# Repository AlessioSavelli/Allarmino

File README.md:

# Welcome to Allarmino  

Benvenuti nel progetto **Allarmino**! Qui troverai tutti i sorgenti **Hardware**, **Software** e **Firmware** necessari per creare e utilizzare il tuo Allarmino.

---

## 📚 **Riferimenti nelle riviste ElettronicaIN**

- 📖 **[Rivista Nr264](https://futuranet.it/prodotto/n-264-maggio-2022/)**: Introduzione alla **main board Allarmino**, basata su ESP32.
- 📖 **[Rivista Nr271](https://futuranet.it/prodotto/n-271-febbraio-2023-marzo-2023)**: Dettagli sulla **scheda di espansione 01** e il primo approccio al software **AllarminoIDE**.

---

## 💾 **Firmware disponibili per ESP32**

| Versione      | Stato            |
|---------------|------------------|
| V1.0          | Disponibile      |
| V1.1.2        | Disponibile      |
| V1.1.3        | Disponibile      |
### ❌ Firmware non più disponibili:

| Versione      | Stato            |
|---------------|------------------|
| V1.1          | Deprecato        |
| V1.1.1        | Deprecato        |

---

## 🖥️ **Software disponibili**

| Versione      | Testato su                   |
|---------------|------------------------------|
| V1.0.0.2      | Win10 64-bit, Win11 64-bit   |

### ❌ Software non più disponibili:

| Versione      | Testato su                   |
|---------------|------------------------------|
| V1.0          | Win11 64-bit                 |
| V1.0.0.1      | Win10 64-bit, Win11 64-bit   |

---

## 🔧 **Hardware disponibili**

| Componente            | Dettagli                                   |
|-----------------------|-------------------------------------------|
| Allarmino Main Board  | Basata su ESP32                           |
| Espansione 01         | CAN BUS 2.0B + Ethernet (W5500, ENC28J60) |

📄 **[Datasheet disponibile (CLICCA QUI)](https://github.com/AlessioSavelli/Allarmino/tree/main/Datasheet/Allarmino/)**

---

## 📝 **Licenza**

### MIT License - Software
Copyright (c) 2022 Alessio Savelli FuturaGroup

Con la presente si concede, a chiunque ottenga una copia di questo software e dei file di documentazione associati (il "Software"), l'autorizzazione a usare gratuitamente il Software senza alcuna limitazione, compresi i diritti di usare, copiare, modificare, unire, pubblicare, distribuire, cedere in sottolicenza e/o vendere copie del Software, nonché di permettere ai soggetti cui il Software è fornito di fare altrettanto, alle seguenti condizioni:

L'avviso di copyright indicato sopra e questo avviso di autorizzazione devono essere inclusi in ogni copia o parte sostanziale del Software.

IL SOFTWARE VIENE FORNITO "COSÌ COM'È", SENZA GARANZIE DI ALCUN TIPO, ESPLICITE O IMPLICITE.

### MIT License - Hardware
Copyright (c) 2022 Alessio Savelli FuturaGroup

Con la presente si concede, a chiunque ottenga una copia di questo hardware e dei file di documentazione associati (l'"Hardware"), l'autorizzazione a usare gratuitamente l'Hardware senza alcuna limitazione, compresi i diritti di usare, copiare, modificare, unire, pubblicare, distribuire, cedere in sottolicenza e/o vendere copie dell'Hardware, nonché di permettere ai soggetti cui l'Hardware è fornito di fare altrettanto, alle seguenti condizioni:

L'avviso di copyright indicato sopra e questo avviso di autorizzazione devono essere inclusi in ogni copia o parte sostanziale dell'Hardware.

L'HARDWARE VIENE FORNITO "COSÌ COM'È", SENZA GARANZIE DI ALCUN TIPO, ESPLICITE O IMPLICITE.

---

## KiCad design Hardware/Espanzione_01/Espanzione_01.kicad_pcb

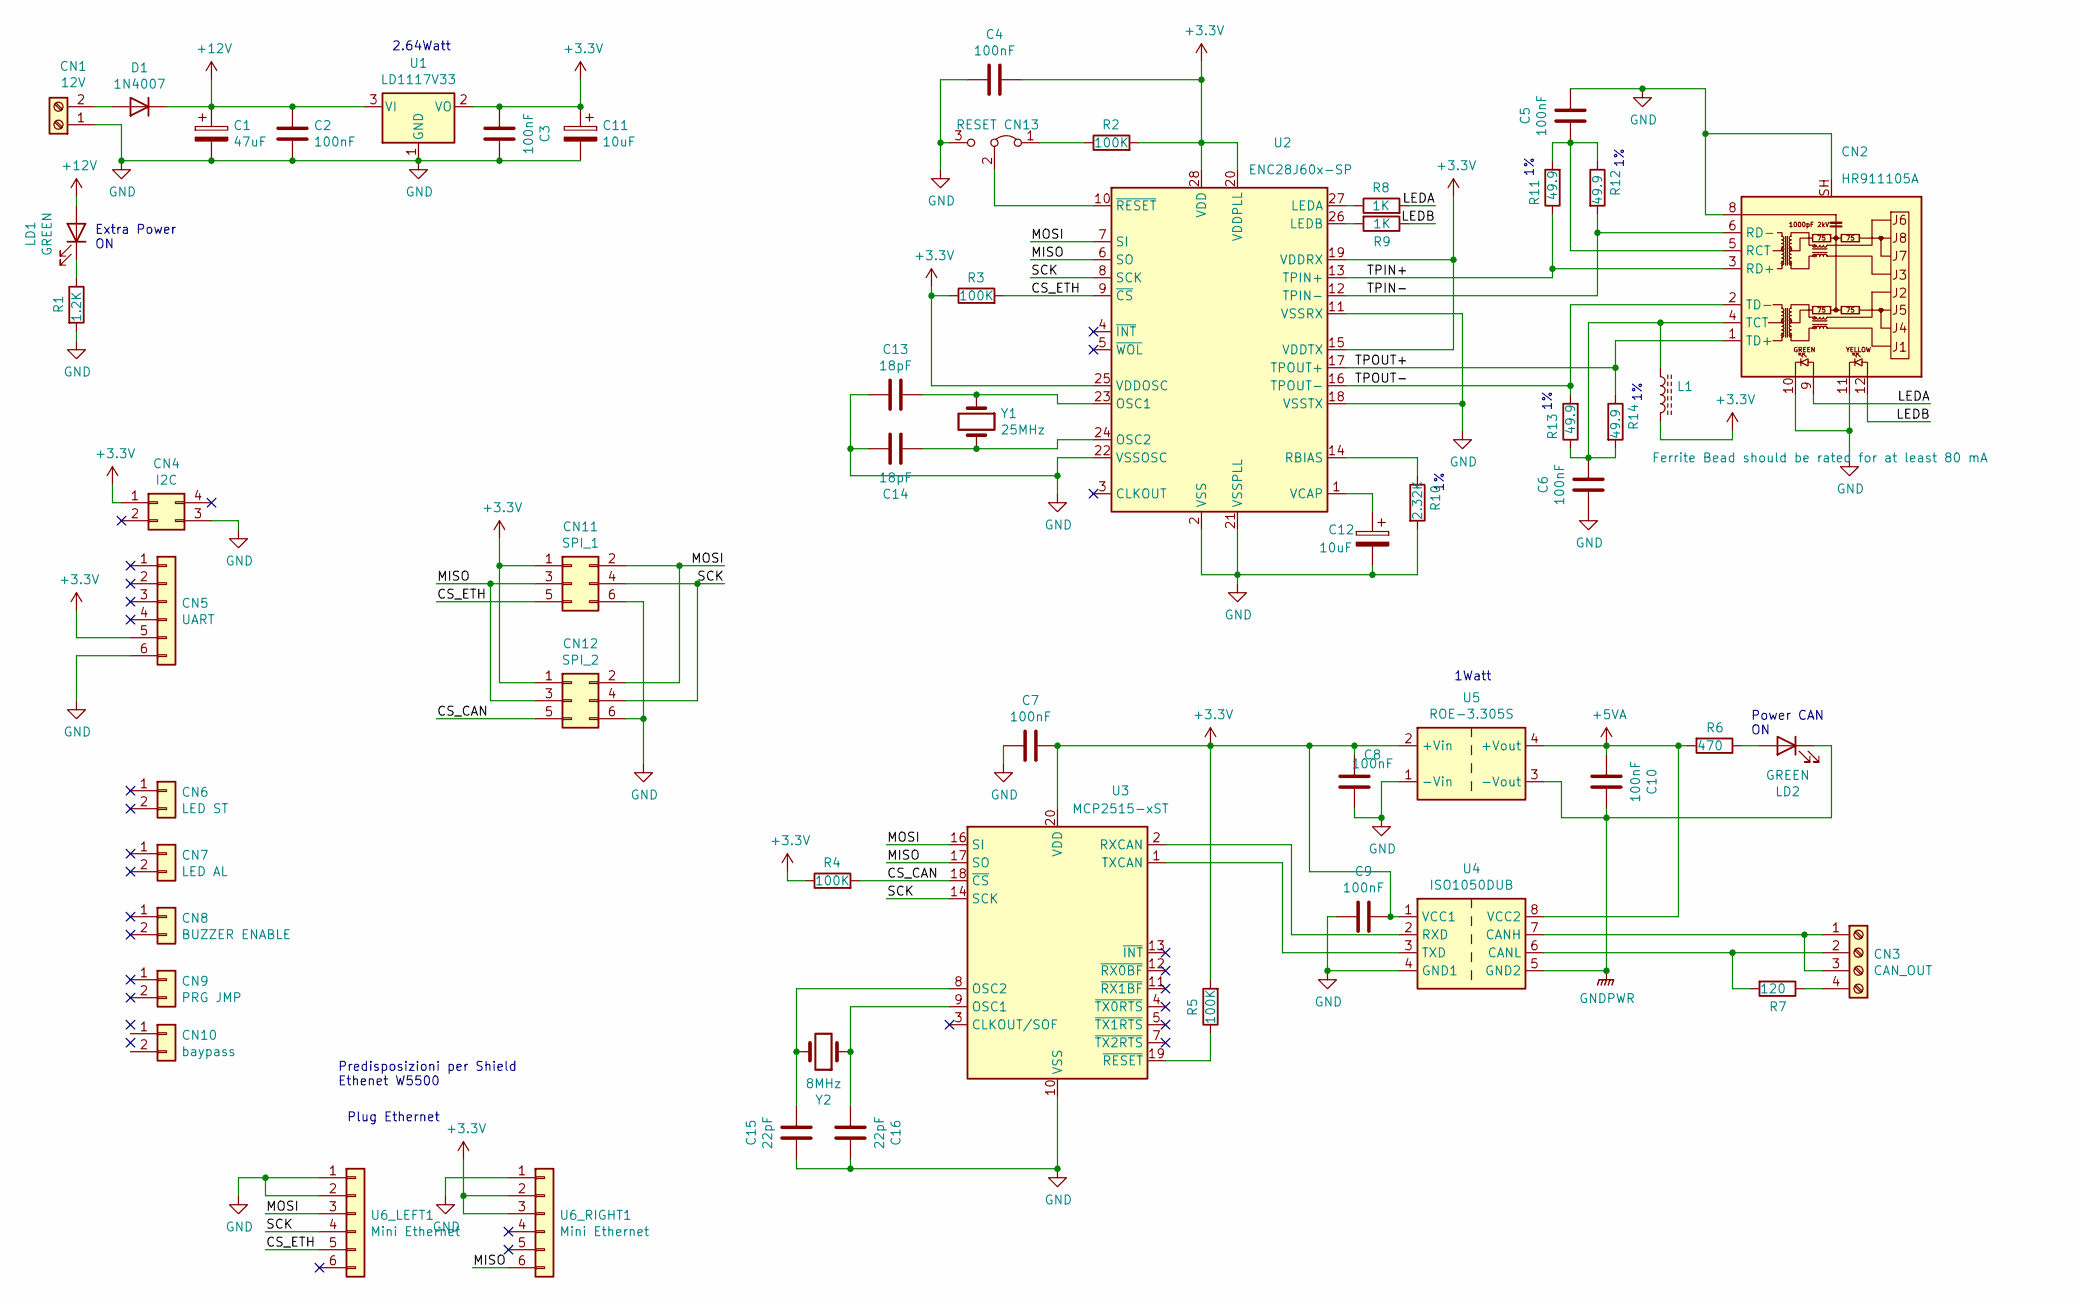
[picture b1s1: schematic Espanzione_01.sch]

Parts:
C1: 47uF; CP_Radial_D8.0mm_P3.50mm
C2, C3, C4, C5, C6, C7, C8, C9, C10: 100nF; C_Disc_D4.7mm_W2.5mm_P5.00mm
C11, C12: 10uF; CP_Radial_D5.0mm_P2.50mm
C13, C14: 18pF; C_Disc_D4.7mm_W2.5mm_P5.00mm
C15, C16: 22pF; C_Disc_D4.7mm_W2.5mm_P5.00mm
CN1: 12V; TerminalBlock_bornier-2_P5.08mm
CN2: HR911105A; RJ45_Wuerth_7499010121A_Horizontal
CN3: CAN_OUT; TerminalBlock_bornier-4_P5.08mm
CN4: I2C; PinHeader_2x02_P2.54mm_Vertical
CN5: UART; PinHeader_1x06_P2.54mm_Vertical
CN6: LED ST; PinHeader_1x02_P2.54mm_Vertical
CN7: LED AL; PinHeader_1x02_P2.54mm_Vertical
CN8: BUZZER ENABLE; PinHeader_1x02_P2.54mm_Vertical
CN9: PRG JMP; PinHeader_1x02_P2.54mm_Vertical
CN10: baypass; PinHeader_1x02_P2.54mm_Vertical
CN11: SPI_1; PinHeader_2x03_P2.54mm_Vertical
CN12: SPI_2; PinHeader_2x03_P2.54mm_Vertical
CN13: RESET; SolderJumper-3_P1.3mm_Bridged12_Pad1.0x1.5mm_NumberLabels
D1: 1N4007; D_DO-41_SOD81_P5.08mm_Vertical_KathodeUp
L1: Ferrite Bead should be rated for at least 80 mA; L_Axial_L7.0mm_D3.3mm_P2.54mm_Vertical_Fastron_MICC
LD1, LD2: GREEN; LED_D3.0mm
R1: 1.2K; R_Axial_DIN0207_L6.3mm_D2.5mm_P2.54mm_Vertical
R2, R3, R4, R5: 100K; R_Axial_DIN0207_L6.3mm_D2.5mm_P2.54mm_Vertical
R6: 470; R_Axial_DIN0207_L6.3mm_D2.5mm_P2.54mm_Vertical
R7: 120; R_Axial_DIN0207_L6.3mm_D2.5mm_P2.54mm_Vertical
R8, R9: 1K; R_Axial_DIN0207_L6.3mm_D2.5mm_P2.54mm_Vertical
R10: 2.32K; R_Axial_DIN0207_L6.3mm_D2.5mm_P2.54mm_Vertical
R11, R12, R13, R14: 49.9; R_Axial_DIN0207_L6.3mm_D2.5mm_P2.54mm_Vertical
U1: LD1117V33; TO-220-3_Horizontal_TabDown
U2: ENC28J60x-SP; DIP-28_W7.62mm
U3: MCP2515-xST; TSSOP-20_4.4x6.5mm_P0.65mm
U4: ISO1050DUB; DIP-8_W7.62mm_Socket
U5: ROE-3.305S; Converter_DCDC_Murata_MEE1SxxxxSC_THT
U6_LEFT1, U6_RIGHT1: Mini Ethernet; PinHeader_1x06_P2.54mm_Vertical
Y1: 25MHz; Crystal_HC49-4H_Vertical
Y2: 8MHz; Crystal_HC49-4H_Vertical

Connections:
+3.3VA: C10.2, R6.2, U4.8 (VCC2), U5.4 (+Vout)
+3V3: C3.2, C4.1, C7.2, C8.1, C9.1, C11.1, CN4.1, CN5.5, CN11.1, CN12.1, L1.2, R2.2, R3.1, R4.1, R5.2, U1.2 (VO), U2.15 (VDDTX), U2.19 (VDDRX), U2.20 (VDDPLL), U2.25 (VDDOSC), U2.28 (VDD), U3.20 (VDD), U4.1 (VCC1), U5.2 (+Vin), U6_RIGHT1.2, U6_RIGHT1.3
+12V: C1.1, C2.1, D1.1 (K), LD1.2 (A), U1.3 (VI)
/CS_CAN: CN12.5, R4.2, U3.18 (~CS)
/CS_ETH: CN11.5, R3.2, U2.9 (~CS), U6_LEFT1.5
/LEDA: CN2.9, R8.2
/LEDB: CN2.12, R9.1
/MISO: CN11.3, CN12.3, U2.6 (SO), U3.17 (SO), U6_RIGHT1.6
/MOSI: CN11.2, CN12.2, U2.7 (SI), U3.16 (SI), U6_LEFT1.3
/SCK: CN11.4, CN12.4, U2.8 (SCK), U3.14 (SCK), U6_LEFT1.4
/TPIN+: CN2.3 (RD+), R11.1, U2.13 (TPIN+)
/TPIN-: CN2.6 (RD-), R12.2, U2.12 (TPIN-)
/TPOUT+: CN2.1 (TD+), R14.1, U2.17 (TPOUT+)
/TPOUT-: CN2.2 (TD-), R13.2, U2.16 (TPOUT-)
GND: C1.2, C2.2, C3.1, C4.2, C5.1, C6.2, C7.1, C8.2, C9.2, C11.2, C12.2, C13.2, C14.1, C15.2, C16.1, CN1.1, CN2.8, CN2.10, CN2.11, CN2.SH, CN4.3, CN5.6, CN11.6, CN12.6, CN13.3 (B), R1.2, R10.2, U1.1 (GND), U2.2 (VSS), U2.11 (VSSRX), U2.18 (VSSTX), U2.21 (VSSPLL), U2.22 (VSSOSC), U3.10 (VSS), U4.4 (GND1), U5.1 (-Vin), U6_LEFT1.1, U6_LEFT1.2, U6_RIGHT1.1
GNDPWR: C10.1, LD2.1 (K), U4.5 (GND2), U5.3 (-Vout)
unnamed: C5.2, CN2.5 (RCT), R11.2, R12.1
unnamed: C6.1, CN2.4 (TCT), L1.1, R13.1, R14.2
unnamed: C12.1, U2.1 (VCAP)
unnamed: C13.1, U2.23 (OSC1), Y1.1
unnamed: C14.2, U2.24 (OSC2), Y1.2
unnamed: C15.1, U3.8 (OSC2), Y2.2
unnamed: C16.2, U3.9 (OSC1), Y2.1
unnamed: CN1.2, D1.2 (A)
unnamed: CN3.1, CN3.3, U4.7 (CANH)
unnamed: CN3.2, R7.2, U4.6 (CANL)
unnamed: CN3.4, R7.1
unnamed: CN13.1 (A), R2.1
unnamed: CN13.2 (C), U2.10 (~RESET)
unnamed: LD1.1 (K), R1.1
unnamed: LD2.2 (A), R6.1
unnamed: R5.1, U3.19 (~RESET)
unnamed: R8.1, U2.27 (LEDA)
unnamed: R9.2, U2.26 (LEDB)
unnamed: R10.1, U2.14 (RBIAS)
unnamed: U3.1 (TXCAN), U4.3 (TXD)
unnamed: U3.2 (RXCAN), U4.2 (RXD)

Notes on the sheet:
2.64Watt
Extra Power ON
Power CAN ON
1Watt
Predisposizioni per Shield Ethenet W5500
Plug Ethernet

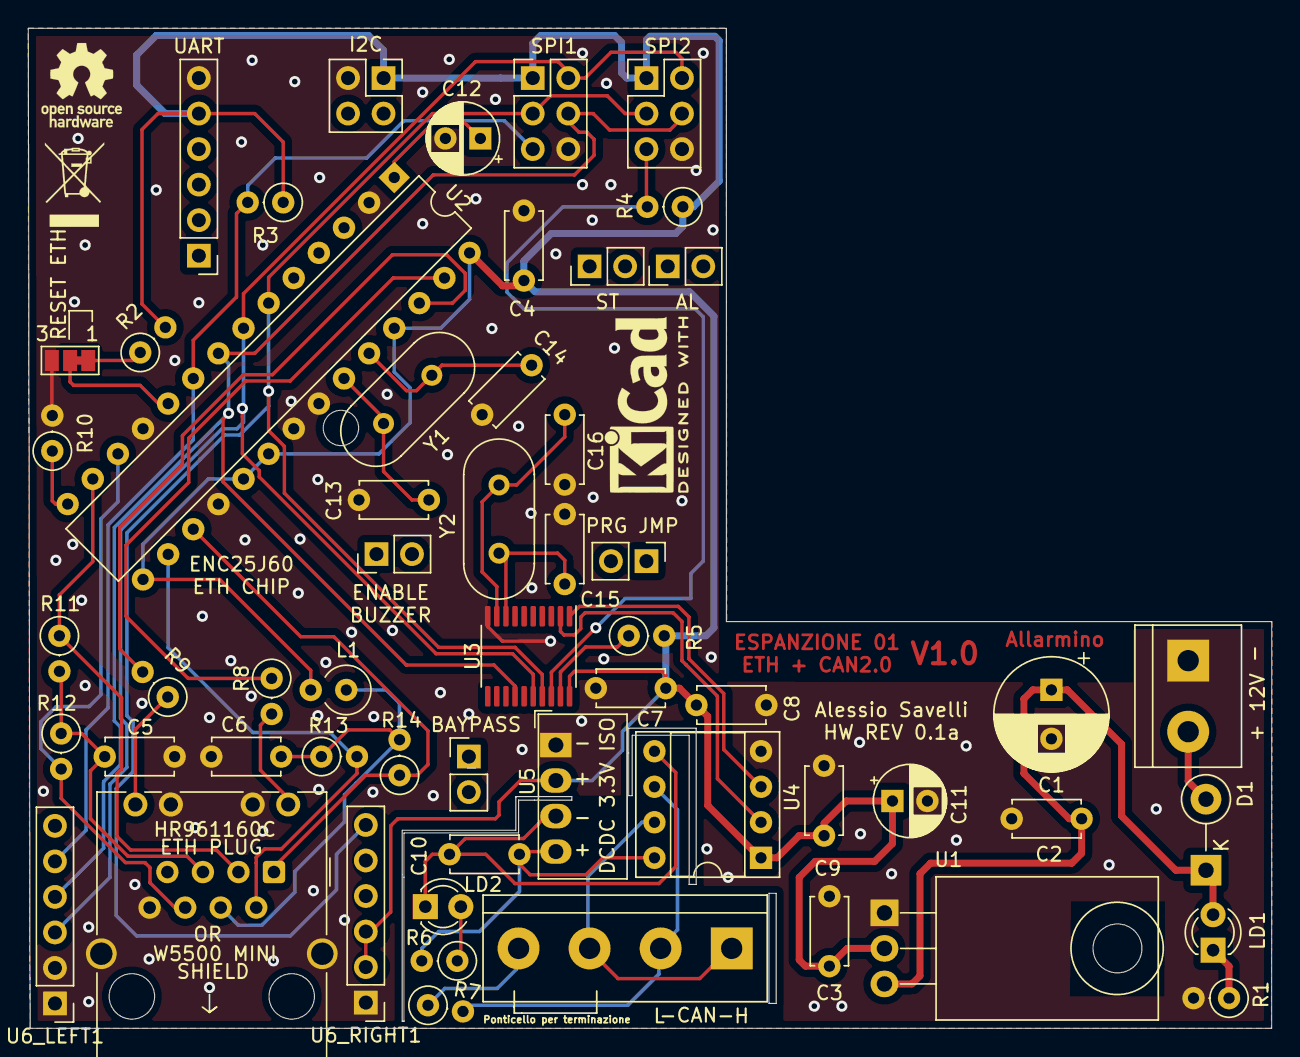
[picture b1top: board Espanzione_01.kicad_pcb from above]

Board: 2 copper layers, 88.9 x 71.5 mm, 56 parts (0 on the bottom side), 37 nets.

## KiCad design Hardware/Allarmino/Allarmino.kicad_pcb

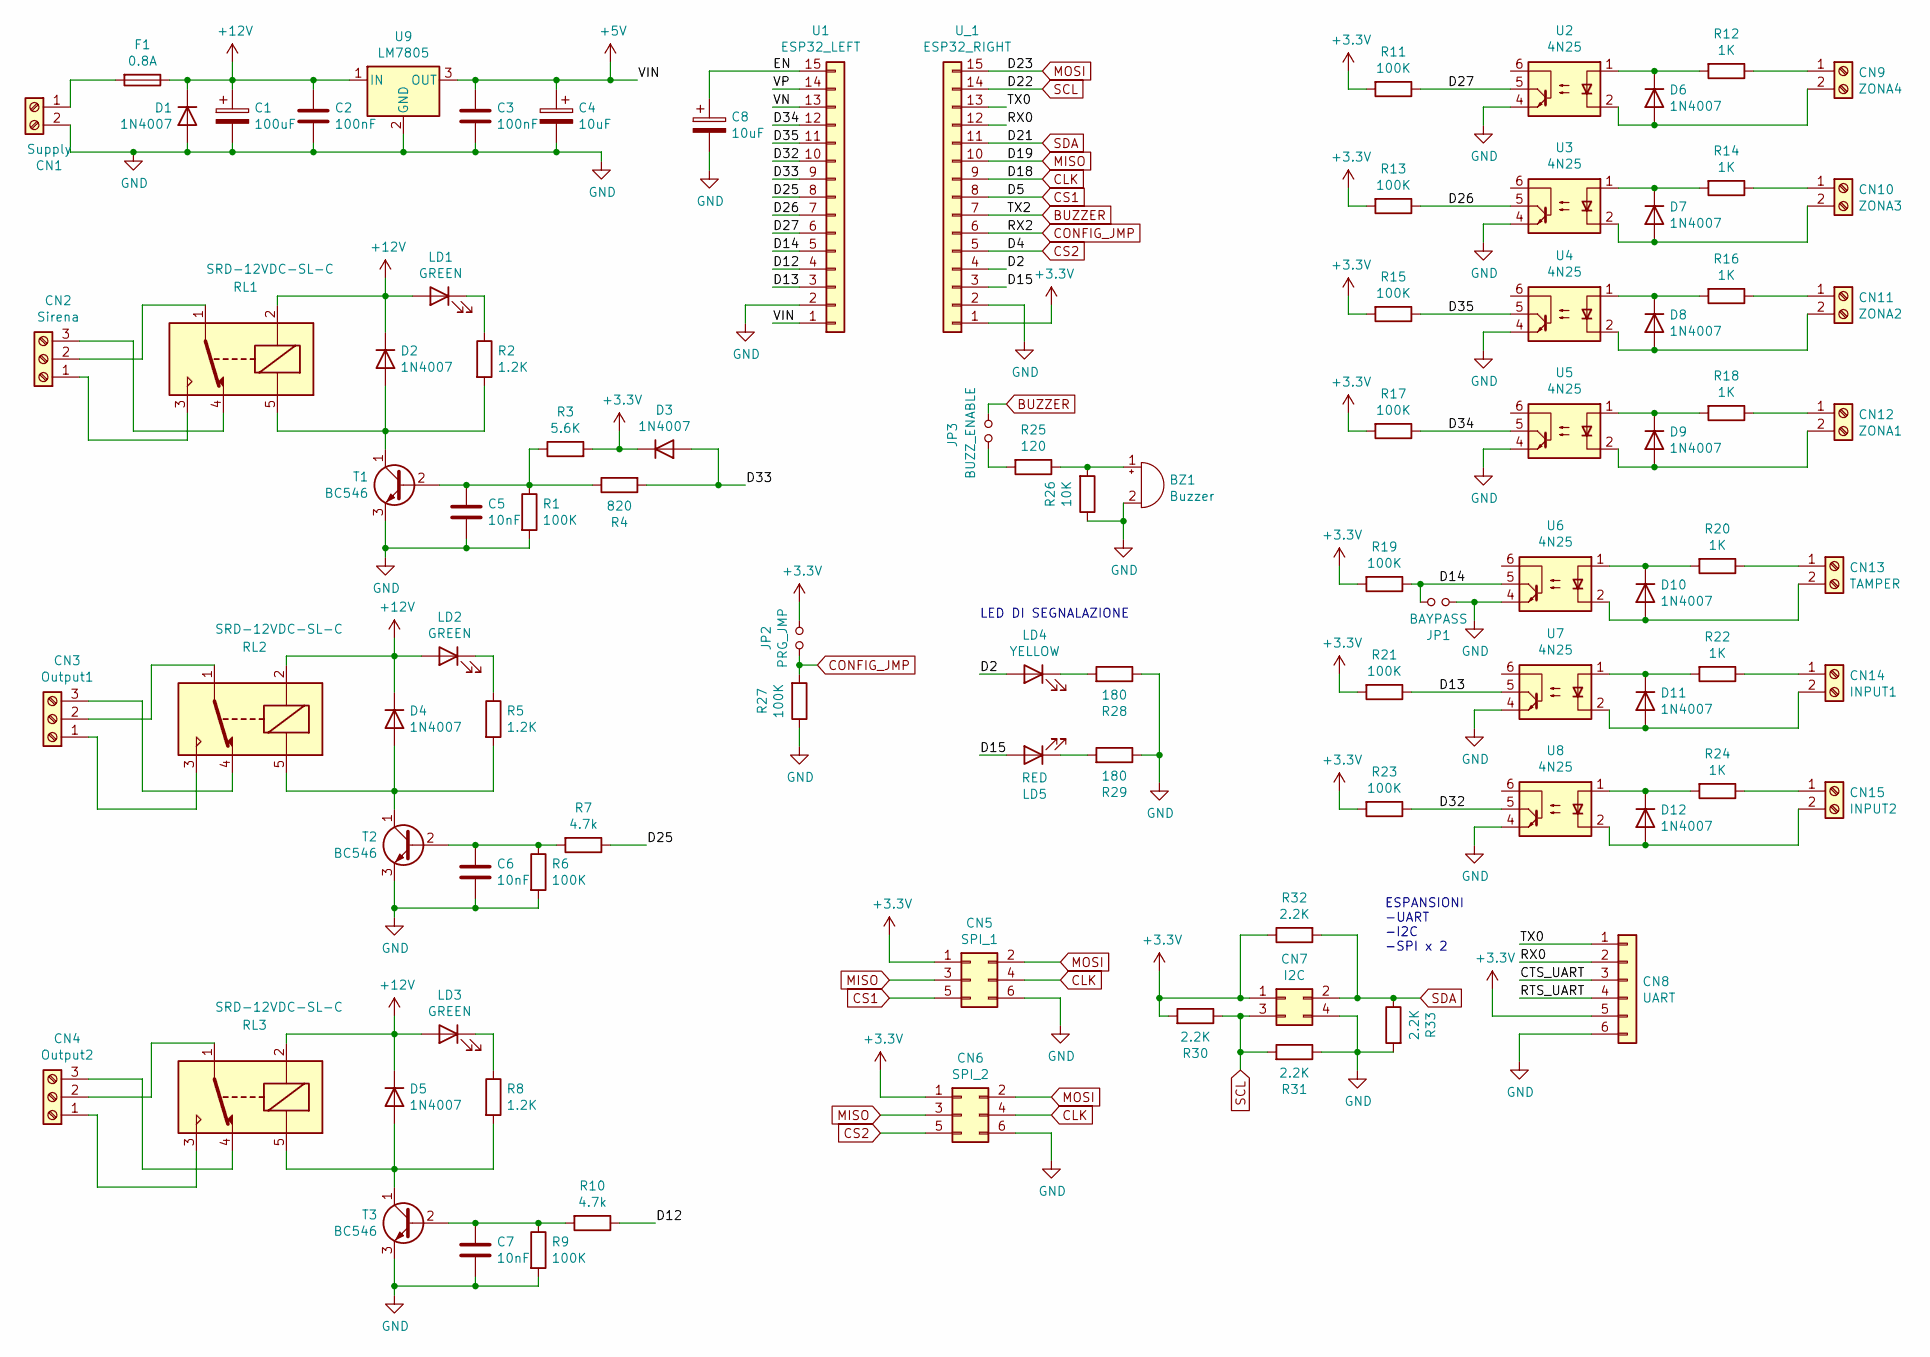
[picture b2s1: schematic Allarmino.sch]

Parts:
BZ1: Buzzer; Buzzer_12x9.5RM7.6
C1: 100uF; CP_Radial_D8.0mm_P3.50mm
C2, C3: 100nF; C_Disc_D4.7mm_W2.5mm_P5.00mm
C4: 10uF; CP_Radial_D6.3mm_P2.50mm
C5, C6, C7: 10nF; C_Disc_D4.7mm_W2.5mm_P5.00mm
C8: 10uF; CP_Radial_D5.0mm_P2.50mm
CN1: Supply; TerminalBlock_Altech_AK300-2_P5.00mm
CN2: Sirena; TerminalBlock_Altech_AK300-3_P5.00mm
CN3: Output1; TerminalBlock_Altech_AK300-3_P5.00mm
CN4: Output2; TerminalBlock_Altech_AK300-3_P5.00mm
CN5: SPI_1; PinHeader_2x03_P2.54mm_Vertical
CN6: SPI_2; PinHeader_2x03_P2.54mm_Vertical
CN7: I2C; PinHeader_2x02_P2.54mm_Vertical
CN8: UART; PinHeader_1x06_P2.54mm_Vertical
CN9: ZONA4; TerminalBlock_Altech_AK300-2_P5.00mm
CN10: ZONA3; TerminalBlock_Altech_AK300-2_P5.00mm
CN11: ZONA2; TerminalBlock_Altech_AK300-2_P5.00mm
CN12: ZONA1; TerminalBlock_Altech_AK300-2_P5.00mm
CN13: TAMPER; TerminalBlock_Altech_AK300-2_P5.00mm
CN14: INPUT1; TerminalBlock_Altech_AK300-2_P5.00mm
CN15: INPUT2; TerminalBlock_Altech_AK300-2_P5.00mm
D1, D2, D3, D4, D5: 1N4007; D_DO-41_SOD81_P10.16mm_Horizontal
D6, D7, D8, D9, D10, D11, D12: 1N4007; D_DO-41_SOD81_P5.08mm_Vertical_KathodeUp
F1: 0.8A; Fuse_Blade_ATO_directSolder
JP1: BAYPASS; PinHeader_1x02_P2.54mm_Vertical
JP2: PRG_JMP; PinHeader_1x02_P2.54mm_Vertical
JP3: BUZZ_ENABLE; PinHeader_1x02_P2.54mm_Vertical
LD1, LD2, LD3: GREEN; LED_D3.0mm
LD4: YELLOW; LED_D3.0mm
LD5: RED; LED_D3.0mm
R1, R6, R9, R11, R13, R15, R17, R19, R21, R23, R27: 100K; R_Axial_DIN0207_L6.3mm_D2.5mm_P10.16mm_Horizontal
R2, R5, R8: 1.2K; R_Axial_DIN0207_L6.3mm_D2.5mm_P10.16mm_Horizontal
R3: 5.6K; R_Axial_DIN0207_L6.3mm_D2.5mm_P10.16mm_Horizontal
R4: 820; R_Axial_DIN0207_L6.3mm_D2.5mm_P10.16mm_Horizontal
R7, R10: 4.7k; R_Axial_DIN0207_L6.3mm_D2.5mm_P10.16mm_Horizontal
R12, R14, R16, R18, R20, R22, R24: 1K; R_Axial_DIN0207_L6.3mm_D2.5mm_P5.08mm_Vertical
R25: 120; R_Axial_DIN0207_L6.3mm_D2.5mm_P10.16mm_Horizontal
R26: 10K; R_Axial_DIN0207_L6.3mm_D2.5mm_P10.16mm_Horizontal
R28, R29: 180; R_Axial_DIN0207_L6.3mm_D2.5mm_P10.16mm_Horizontal
R30, R31, R32, R33: 2.2K; R_Axial_DIN0207_L6.3mm_D2.5mm_P10.16mm_Horizontal
RL1, RL2, RL3: SRD-12VDC-SL-C; Relay_SPDT_Omron-G5LE-1
T1, T2, T3: BC546; TO-92_Inline
U1: ESP32_LEFT; PinHeader_1x15_P2.54mm_Vertical
U2, U3, U4, U5, U6, U7, U8: 4N25; DIP-6_W7.62mm
U9: LM7805; TO-220-3_Vertical
U_1: ESP32_RIGHT; PinHeader_1x15_P2.54mm_Vertical

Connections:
+3V3: CN5.1, CN6.1, CN7.1, CN8.5, D3.1 (K), JP2.2, R3.2, R11.2, R13.2, R15.2, R17.2, R19.2, R21.2, R23.2, R30.2, R32.1, U_1.1
+5V: C3.1, C4.1, U1.1, U9.3 (OUT)
+12V: C1.1, C2.1, D1.1 (K), D2.1 (K), D4.1 (K), D5.1 (K), F1.1, LD1.2 (A), LD2.2 (A), LD3.2 (A), RL1.2, RL2.2, RL3.2, U9.1 (IN)
/CTS_UART: CN8.3
/D2: LD4.2 (A), U_1.4
/D12: R10.1, U1.4
/D13: R21.1, U1.3, U7.5
/D14: JP1.1, R19.1, U1.5, U6.5
/D15: LD5.2 (A), U_1.3
/D25: R7.1, U1.8
/D26: R13.1, U1.7, U3.5
/D27: R11.1, U1.6, U2.5
/D32: R23.1, U1.10, U8.5
/D33: D3.2 (A), R4.2, U1.9
/D34: R17.1, U1.12, U5.5
/D35: R15.1, U1.11, U4.5
/EN: C8.1, U1.15
/RTS_UART: CN8.4
/RX0: CN8.2, U_1.12
/TX0: CN8.1, U_1.13
/VN: U1.13
/VP: U1.14
BUZZER: JP3.2, U_1.7
CLK: CN5.4, CN6.4, U_1.9
CONFIG_JMP: JP2.1, R27.2, U_1.6
CS1: CN5.5, U_1.8
CS2: CN6.5, U_1.5
GND: BZ1.2 (+), C1.2, C2.2, C3.2, C4.2, C5.2, C6.2, C7.2, C8.2, CN1.2, CN5.6, CN6.6, CN7.4, CN8.6, D1.2 (A), JP1.2, R1.2, R6.2, R9.2, R26.1, R27.1, R28.1, R29.1, R31.1, R33.2, T1.3 (E), T2.3 (E), T3.3 (E), U1.2, U2.4, U3.4, U4.4, U5.4, U6.4, U7.4, U8.4, U9.2 (GND), U_1.2
MISO: CN5.3, CN6.3, U_1.10
MOSI: CN5.2, CN6.2, U_1.15
unnamed: BZ1.1 (-), R25.1, R26.2
unnamed: C5.1, R1.1, R3.1, R4.1, T1.2 (B)
unnamed: C6.1, R6.1, R7.2, T2.2 (B)
unnamed: C7.1, R9.1, R10.2, T3.2 (B)
unnamed: CN1.1, F1.2
unnamed: CN2.1, RL1.3
unnamed: CN2.2, RL1.1
unnamed: CN2.3, RL1.4
unnamed: CN3.1, RL2.3
unnamed: CN3.2, RL2.1
unnamed: CN3.3, RL2.4
unnamed: CN4.1, RL3.3
unnamed: CN4.2, RL3.1
unnamed: CN4.3, RL3.4
unnamed: CN9.1, R12.1
unnamed: CN9.2, D6.2 (A), U2.2
unnamed: CN10.1, R14.1
unnamed: CN10.2, D7.2 (A), U3.2
unnamed: CN11.1, R16.1
unnamed: CN11.2, D8.2 (A), U4.2
unnamed: CN12.1, R18.1
unnamed: CN12.2, D9.2 (A), U5.2
unnamed: CN13.1, R20.1
unnamed: CN13.2, D10.2 (A), U6.2
unnamed: CN14.1, R22.1
unnamed: CN14.2, D11.2 (A), U7.2
unnamed: CN15.1, R24.1
unnamed: CN15.2, D12.2 (A), U8.2
unnamed: D2.2 (A), R2.2, RL1.5, T1.1 (C)
unnamed: D4.2 (A), R5.2, RL2.5, T2.1 (C)
unnamed: D5.2 (A), R8.2, RL3.5, T3.1 (C)
unnamed: D6.1 (K), R12.2, U2.1
unnamed: D7.1 (K), R14.2, U3.1
unnamed: D8.1 (K), R16.2, U4.1
unnamed: D9.1 (K), R18.2, U5.1
unnamed: D10.1 (K), R20.2, U6.1
unnamed: D11.1 (K), R22.2, U7.1
unnamed: D12.1 (K), R24.2, U8.1
unnamed: JP3.1, R25.2
unnamed: LD1.1 (K), R2.1
unnamed: LD2.1 (K), R5.1
unnamed: LD3.1 (K), R8.1
unnamed: LD4.1 (K), R28.2
unnamed: LD5.1 (K), R29.2
SCL: CN7.3, R30.1, R31.2, U_1.14
SDA: CN7.2, R32.2, R33.1, U_1.11

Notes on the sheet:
LED DI SEGNALAZIONE
ESPANSIONI -UART -I2C -SPI x 2

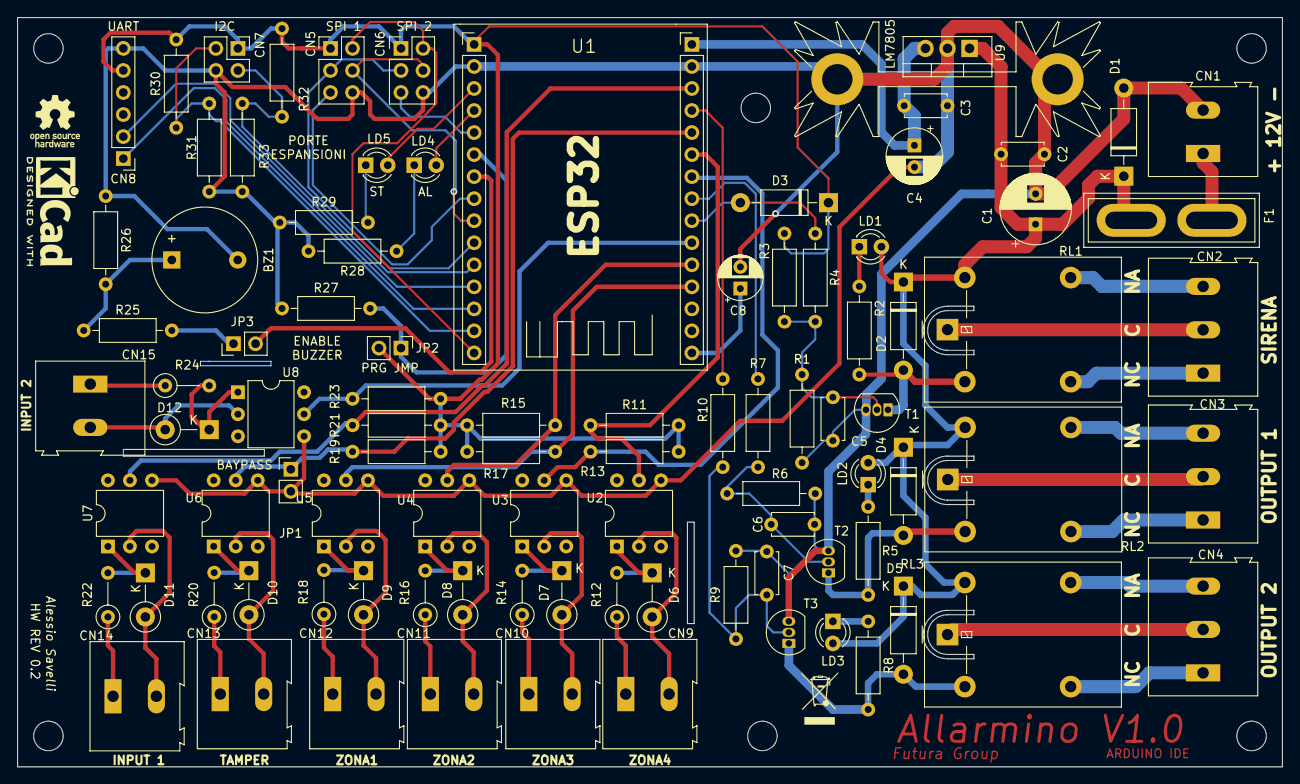
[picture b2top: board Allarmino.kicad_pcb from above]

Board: 2 copper layers, 145.8 x 86.4 mm, 94 parts (0 on the bottom side), 72 nets.

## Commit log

2022-08-03 Frist Pull
    Upload solo hardware
2022-08-03 Frist Pull
    Caricamento dei Firmware
2022-08-03 Frist Pull
    Caricamento Software pt1
2022-08-03 Rename Info.txt to Info.MD
2022-08-03 Rename Info.MD to README.md
2022-08-03 Allineamento
2022-08-03 Rename LICENZA.txt to README.md
2022-08-03 Frist Relase
    publicazzione Software pt4
2022-10-23 Datasheet
    Add datasheet for allarmino Rev1 ITA
2022-10-23 Datasheet
2022-11-01 Firmware V1.1.1 Relase
    Rilascio nuovo firmware.
    FIX bug pilotaggio output con Telegram
2022-11-01 Fix 1.1.1V
2022-11-04 Relase FW 1.1.2 e SW 1.0.0.1
    [Software]
    relase V1.0.0.1
    -Fix Ide Portable per il Software. Testato su Win11 e Win10
    -Aggiunta disponibilità del firmware V1.1.2 nel software
    [Firmware]
    -Fix bug compatibilità NTP con Ethernet UDP
2022-11-04 Relase Compiled SW 1.0.0.1
2022-11-05 Aggiornamento Datasheet Allarmino
2022-11-05 remove
2022-11-06 Aggiornamento Schemi di cablaggio
    Migliorata qualita' degli schemi.
2022-12-11 Relase Driver per il Software
    Aggiunta cartella driver nella Relase SW per installare il NetCore 3.1 e i vari driver dell'ESP32
2024-12-13 Relase Allarmino V1.1.3
    Fix bugs and update cast convertion for new IDE
2024-12-13 Upload Version1.0.0.2
    part 1
2024-12-13 part1
2024-12-14 alling

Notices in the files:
README.md:
License: MIT License
